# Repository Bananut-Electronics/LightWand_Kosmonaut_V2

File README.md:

# LightWand_Kosmonaut_V2

Welcome to the LightWand_Kosmonaut_V2 repository. Careful traveller! It is still under development

This _Wiki_ covers the _**LightWand Kosmonaut V2**_ lightpainting tool, an _Open Source_, cheap, easy to made and modify machine tu help the user make awesome detailled photographs through the lightpainting technique.

# What is the LightWand Kosmonaut V2?
The _**LightWand Kosmonaut V2(LWK2)**_ is an Arduino based device which can control LED Stripes in order to display images stored in an SD card. Additionally, it has a number of additional features to use it as a sensor data display device or a simple pattern generator for lightpainting photography.

# So, if this one is V2... where is V1?
The _**LightWand Kosmonaut V1(LWK1)**_ was developped by Pablo dMM in 2015 (The same guy that developped this one) and the repository can be found here:

https://github.com/PabloDMM/LightWand_KosmonautEd

This project was originally based on the first _LightWand_ made by _**Michael Ross**_ in 2014 (http://mrossphoto.com/wordpress32/), please check out his awesome work. The LWK1 inherited form this version the main concept and two SW functions (described in code).

It is a similar tool to the commercial product _**Pixelstick**_ (http://www.thepixelstick.com/).

# Show me what can be done with it.
These are some photos made with this tools, and that should guide you an idea of what is it and how could it be used. None of these photos are processed (further that contrast and brightness and perhaps saturation):

# What license does it have?
The _**LightWand Kosmonaut V2**_ has a _**CC BY-NC-AT 4.0**_ (https://creativecommons.org/licenses/by/4.0/legalcode)

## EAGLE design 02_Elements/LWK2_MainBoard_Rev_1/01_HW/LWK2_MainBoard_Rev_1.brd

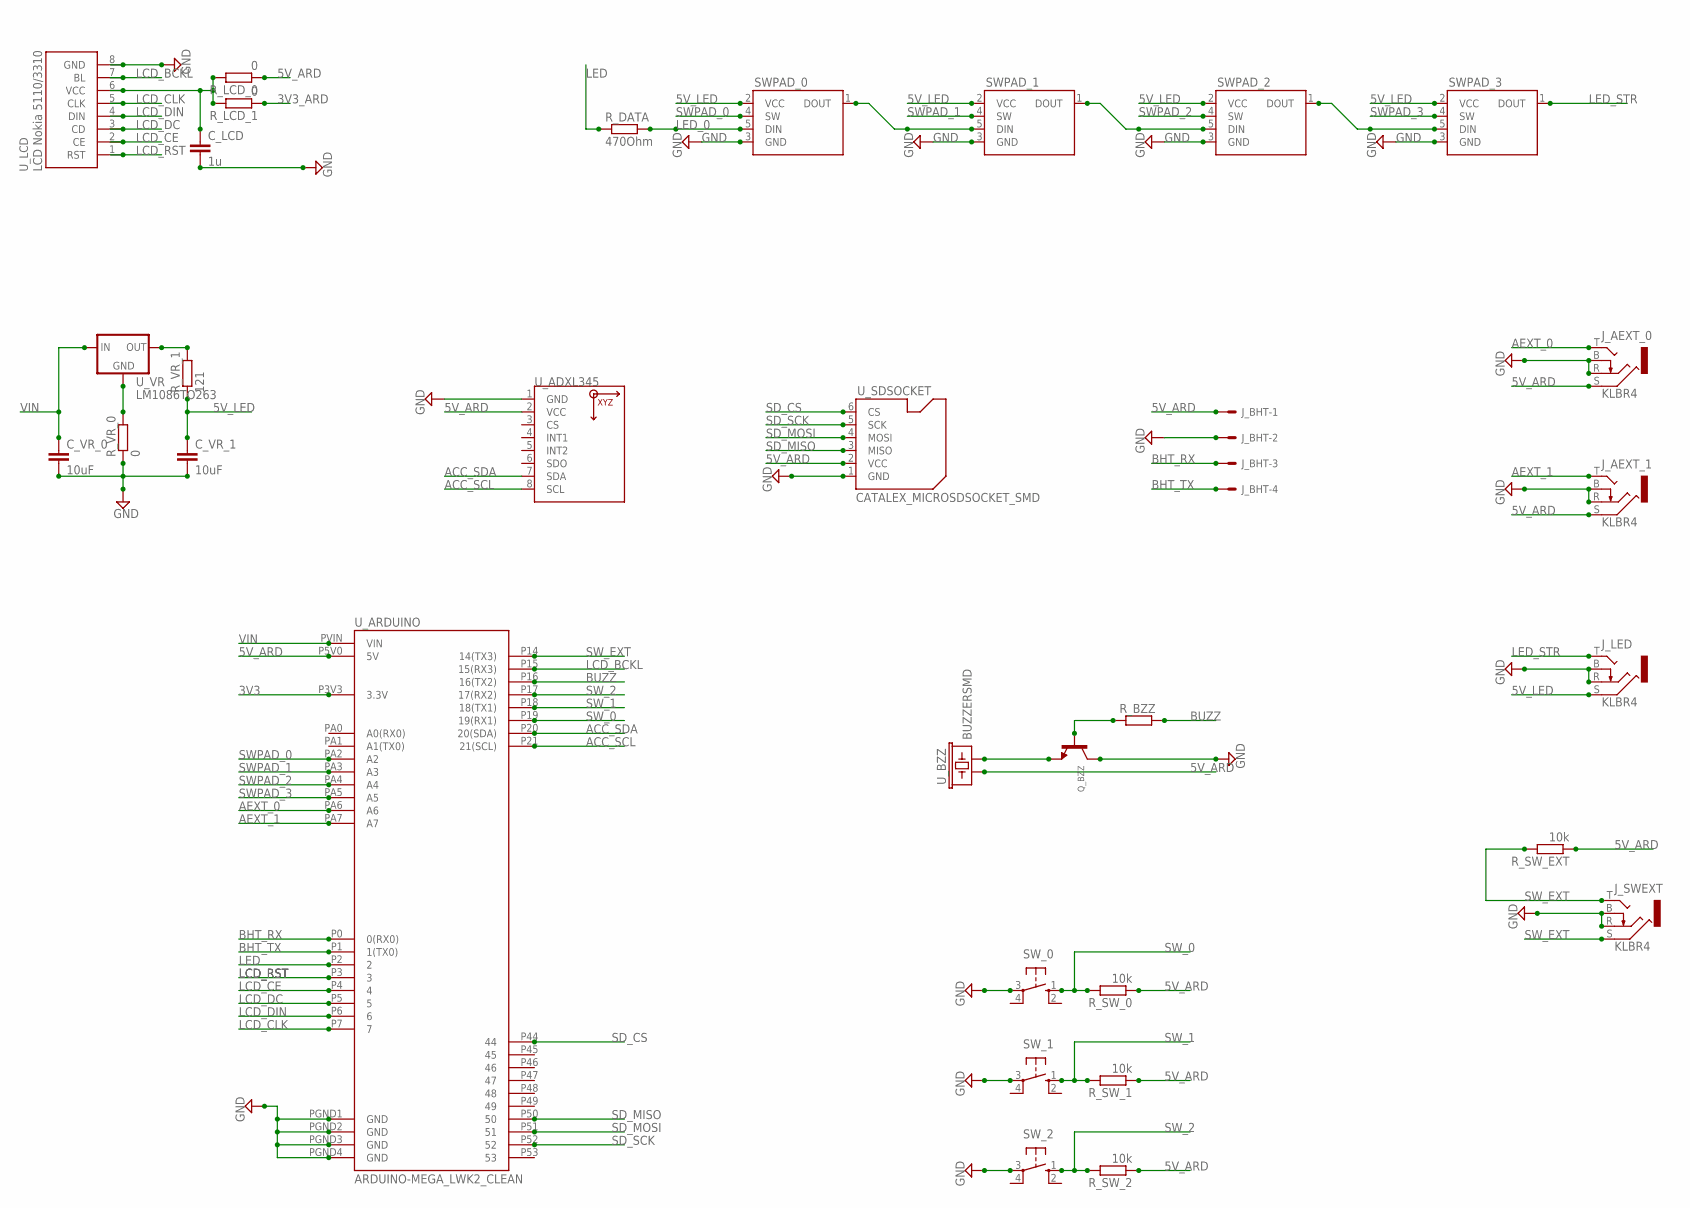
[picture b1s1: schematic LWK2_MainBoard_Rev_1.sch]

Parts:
C_LCD: 1u; C1206
C_VR_0, C_VR_1: 10uF; C1206
J_AEXT_0, J_AEXT_1: KLBR4
J_BHT: 22-05-7048-04; 7395-04
J_LED: KLBR4
J_SWEXT: KLBR4
Q_BZZ: TRANSISTOR_NPNWIDE; SOT23-WIDE
R_BZZ: R-EU_R1206; R1206
R_DATA: 470Ohm; R1206
R_LCD_0, R_LCD_1: 0; R1206
R_SW_0, R_SW_1, R_SW_2: 10k; R1206
R_SW_EXT: 10k; R1206
R_VR_0: 0; R1206
R_VR_1: 121; R1206
SWPAD_0, SWPAD_1, SWPAD_2, SWPAD_3: MDM_V3_LEDPAD
SW_0, SW_1, SW_2: 40-XX-ROUND; B3F-40XX-ROUND
U_ADXL345: GY-291_ADXL345
U_ARDUINO: ARDUINO-MEGA_LWK2_CLEAN; ARDUINO_MEGA_LWK2_CLEAN
U_BZZ: BUZZERSMD; BUZZER-CMT1603
U_LCD: NOKIA5110
U_SDSOCKET: CATALEX_MICROSDSOCKET_SMD
U_VR: LM1086TO263; TO263

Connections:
3V3: U_ARDUINO.P3V3 (3.3V)
3V3_ARD: R_LCD_1.1
5V_ARD: J_AEXT_0.S, J_AEXT_1.S, J_BHT.1, R_LCD_0.1, R_SW_0.1, R_SW_1.1, R_SW_2.1, R_SW_EXT.1, U_ADXL345.2 (VCC), U_ARDUINO.P5V0 (5V), U_BZZ.P$1 (1), U_SDSOCKET.2 (VCC)
5V_LED: C_VR_1.1, J_LED.S, R_VR_1.1, SWPAD_0.2 (VCC), SWPAD_1.2 (VCC), SWPAD_2.2 (VCC), SWPAD_3.2 (VCC)
ACC_SCL: U_ADXL345.8 (SCL), U_ARDUINO.P21 (21(SCL))
ACC_SDA: U_ADXL345.7 (SDA), U_ARDUINO.P20 (20(SDA))
AEXT_0: J_AEXT_0.T, U_ARDUINO.PA6 (A6)
AEXT_1: J_AEXT_1.T, U_ARDUINO.PA7 (A7)
BHT_RX: J_BHT.3, U_ARDUINO.P0 (0(RX0))
BHT_TX: J_BHT.4, U_ARDUINO.P1 (1(TX0))
BUZZ: R_BZZ.2, U_ARDUINO.P16 (16(TX2))
CS: U_ADXL345.3 (CS)
GND: C_LCD.2, C_VR_0.2, C_VR_1.2, J_AEXT_0.B, J_AEXT_0.R, J_AEXT_1.B, J_AEXT_1.R, J_BHT.2, J_LED.B, J_LED.R, J_SWEXT.B, J_SWEXT.R, Q_BZZ.3 (C), R_VR_0.1, SWPAD_0.3 (GND), SWPAD_1.3 (GND), SWPAD_2.3 (GND), SWPAD_3.3 (GND), SW_0.3, SW_1.3, SW_2.3, U_ADXL345.1 (GND), U_ARDUINO.PGND1 (GND), U_ARDUINO.PGND2 (GND), U_ARDUINO.PGND3 (GND), U_ARDUINO.PGND4 (GND), U_LCD.8 (GND), U_SDSOCKET.1 (GND)
INT1: U_ADXL345.4 (INT1)
INT2: U_ADXL345.5 (INT2)
LCD_BCKL: U_ARDUINO.P15 (15(RX3)), U_LCD.7 (BL)
LCD_CE: U_ARDUINO.P4 (4), U_LCD.2 (CE)
LCD_CLK: U_ARDUINO.P7 (7), U_LCD.5 (CLK)
LCD_DC: U_ARDUINO.P5 (5), U_LCD.3 (CD)
LCD_DIN: U_ARDUINO.P6 (6), U_LCD.4 (DIN)
LCD_PW: C_LCD.1, R_LCD_0.2, R_LCD_1.2, U_LCD.6 (VCC)
LCD_RST: U_ARDUINO.P3 (3), U_LCD.1 (RST)
LED: R_DATA.1, U_ARDUINO.P2 (2)
LED_0: R_DATA.2, SWPAD_0.5 (DIN)
LED_1: SWPAD_0.1 (DOUT), SWPAD_1.5 (DIN)
LED_2: SWPAD_1.1 (DOUT), SWPAD_2.5 (DIN)
LED_3: SWPAD_2.1 (DOUT), SWPAD_3.5 (DIN)
LED_STR: J_LED.T, SWPAD_3.1 (DOUT)
unnamed: R_VR_0.2, U_VR.1 (GND)
unnamed: R_VR_1.2, U_VR.2 (OUT)
unnamed: Q_BZZ.2 (E), U_BZZ.P$2 (2)
unnamed: Q_BZZ.1 (B), R_BZZ.1
SDO: U_ADXL345.6 (SDO)
SD_CS: U_ARDUINO.P44 (44), U_SDSOCKET.6 (CS)
SD_MISO: U_ARDUINO.P50 (50), U_SDSOCKET.3 (MISO)
SD_MOSI: U_ARDUINO.P51 (51), U_SDSOCKET.4 (MOSI)
SD_SCK: U_ARDUINO.P52 (52), U_SDSOCKET.5 (SCK)
SWPAD_0: SWPAD_0.4 (SW), U_ARDUINO.PA2 (A2)
SWPAD_1: SWPAD_1.4 (SW), U_ARDUINO.PA3 (A3)
SWPAD_2: SWPAD_2.4 (SW), U_ARDUINO.PA4 (A4)
SWPAD_3: SWPAD_3.4 (SW), U_ARDUINO.PA5 (A5)
SW_0: R_SW_0.2, SW_0.1 (S), U_ARDUINO.P19 (19(RX1))
SW_1: R_SW_1.2, SW_1.1 (S), U_ARDUINO.P18 (18(TX1))
SW_2: R_SW_2.2, SW_2.1 (S), U_ARDUINO.P17 (17(RX2))
SW_EXT: J_SWEXT.S, J_SWEXT.T, R_SW_EXT.2, U_ARDUINO.P14 (14(TX3))
VIN: C_VR_0.1, U_ARDUINO.PVIN (VIN), U_VR.3 (IN)

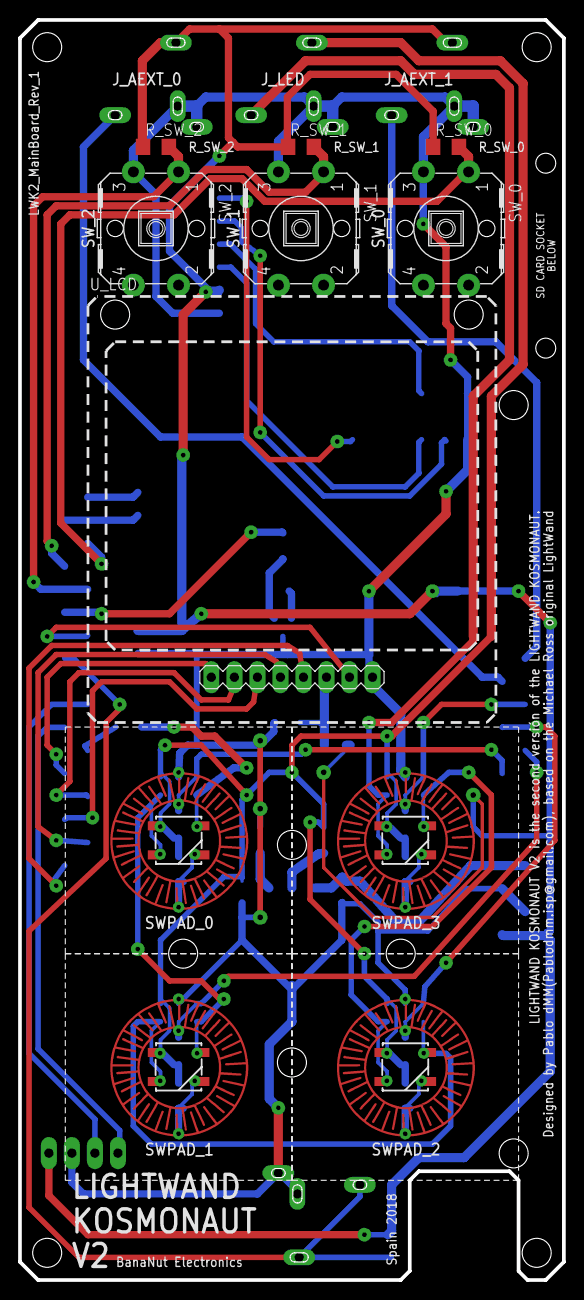
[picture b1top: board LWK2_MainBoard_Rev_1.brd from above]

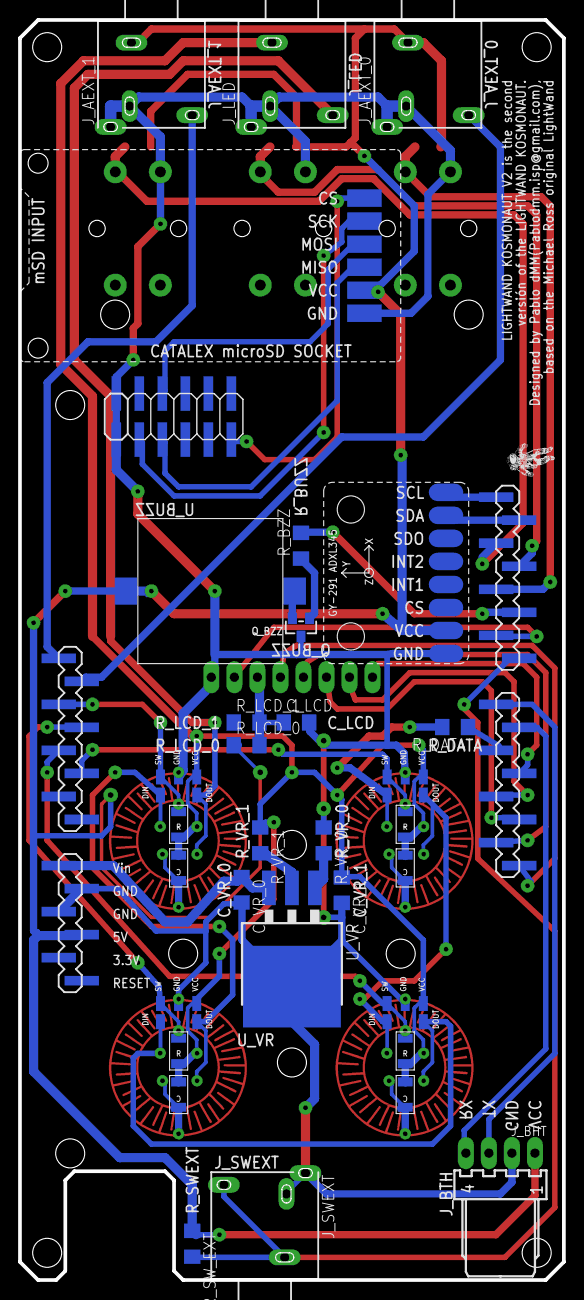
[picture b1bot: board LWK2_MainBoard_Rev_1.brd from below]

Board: 2 copper layers, 60.0 x 139.0 mm, 32 parts (20 on the bottom side), 40 nets.

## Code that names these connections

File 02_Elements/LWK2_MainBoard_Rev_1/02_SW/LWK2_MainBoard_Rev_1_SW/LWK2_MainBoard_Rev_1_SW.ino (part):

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
// LWK2_MainBoard_Rev_1 Pin Definition
const int LCD_SCK =  7;   // Definition of LCD Pins
const int LCD_DIN =  6;   // Definition of LCD Pins
const int LCD_DC  =  5;   // Definition of LCD Pins
const int LCD_CS  =  4;   // Definition of LCD Pins
const int LCD_RST =  3;   // Definition of LCD Pins
const int LCD_BL  = 15;   // Definition of LCD Pins
const int SD_MOSI = 51;   // Definition of SD Pins (Just for Info, already set in the SD library)
const int SD_MISO = 50;   // Definition of SD Pins (Just for Info, already set in the SD library)
const int SD_CLK  = 52;   // Definition of SD Pins (Just for Info, already set in the SD library)
const int SD_CS   = 44;   // Definition of SD Pins (Just for Info, already set in the SD library)
const int SWPad_0 = 56;   // SW LED PAD A SWPad_UP (TOP-LEFT)
const int SWPad_1 = 57;   // SW LED PAD B SWPad_DW (BOT-LEFT)
const int SWPad_2 = 58;   // SW LED PAD C SWPad_EXT (TOP-RIGHT)
const int SWPad_3 = 59;   // SW LED PAD D SWPad_SEL (BOT-RIGHT)
const int SW_2    = 17;   // SW Tactile LEFT
const int SW_1    = 18;   // SW Tactile CENTER
const int SW_0    = 19;   // SW Tactile RIGHT
const int SW_EXT  = 60;   // SW Exterior
const int BUZZ    = 16;   // Buzzer Speaker

// Constant Parameters and values
const int LED_SWPAD    =   4; // Number of WS2812B LEDs in the SW LED Pads
const int LED_STR      = 144; // Number of WS2812B LEDs in the LED Stripe

// Constant BMP
const int BYTE_BMP_HEADER            = 122;  // Header for the Windows BitMap with no Opacity STILL DOUBTS
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                                  {MENU_2_R, MENU_2_G, MENU_2_B}};

// Flags for the Pulse Conformer
int SWPad[4]         = {SWPad_0, SWPad_1, SWPad_2, SWPad_3}; // SWPad Pin Array
boolean SWPad_p[4]   = {false, false, false, false};         // SWPad Pulse Conformer Array

const int SWPad_UP      = 0;
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}

void setupSDcard(){
  pinMode(SD_CS, OUTPUT);
  // SD Initialization Routine
  if (!SD.begin(SD_CS)) 
  {
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
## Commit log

2018-02-24 First Upload
    First upload of current state of the project:
    - HW is done and tested
    - SW still underconstruction
2018-02-27 update Readme
    Not much added, further development
2018-03-01 Further Development
    Updated:
    - Final HW of LWK2_MainBoard_Rev_1
    - Final Housing of LWK2_MainBoard_Rev_1 (print with MDF 2MM)
    - Cleaned folders
    - Added photos for the WIKI
2018-03-04 First Reliable Code
    First basic code. Needs some improvement but it works with .pnm files.
    - Acc not supported yet
2018-03-06 SW Update
    Stable version that reads .bmp files with Windows 32bit depth.
    Minor features added or fixed.
2018-03-06 Added Final Version
    More Stability and stuff
2018-03-07 SW Update
    Now supported .bmp and Color Pattern. I know the explenations are bad but I am the only one listening.
2018-03-11 Documentation Update
    New product photos and refurbished yet still not finished 3D model
2018-03-11 Updated with intro
    Added photos, possible nedd of resize
2018-07-08 Color Gamma Fixed
    Added Gamma Color correction LUT.
    Added images for tutorial
2021-02-09 Updated SW
    Backup

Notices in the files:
02_Elements/LWK2_MainBoard_Rev_1/01_HW/LWK2_MainBoard_Rev_1.sch:
CC BY-NC-SA 4.0
parts and their libraries:
SparkFun: Licensing: CC v3.0 Share-Alike You are welcome to use this library for commercial purposes.
microbuilder: This work is placed in the public domain, and may be freely used for commercial and non-commercial work with the following conditions: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
